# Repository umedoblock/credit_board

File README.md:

# credit_board
This is a credit board. It assure to normal run.

Now credit_board assure you to make some clocks.
Right side can make some clocks that are 10 MHz, 4 MHz, 20 MHz.
Left side can make 32.768 kHz.

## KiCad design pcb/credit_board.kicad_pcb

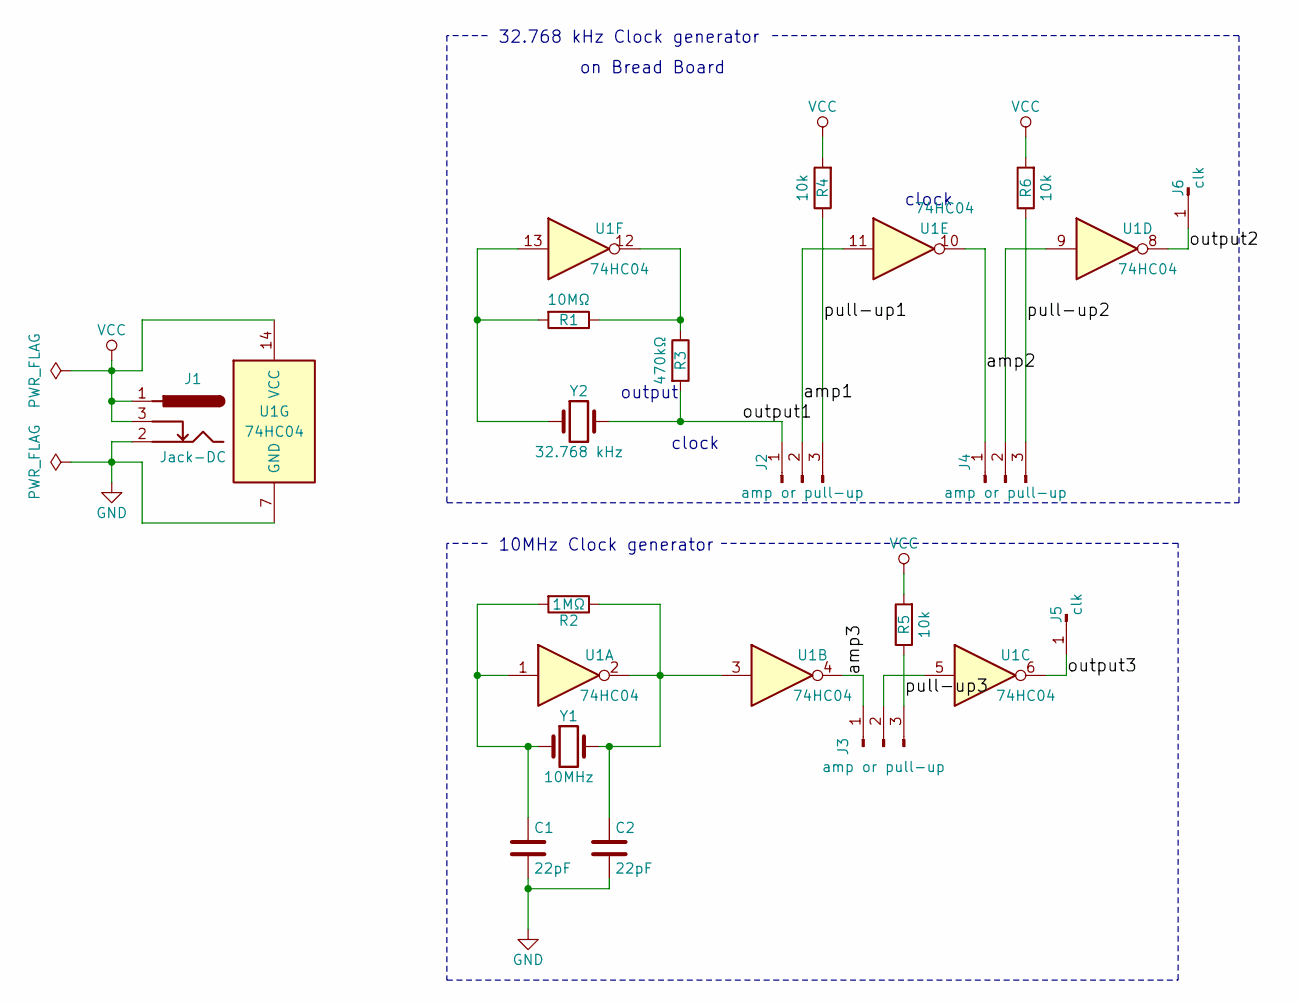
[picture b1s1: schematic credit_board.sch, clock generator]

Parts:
C1, C2: 22pF; C_Disc_D4.7mm_W2.5mm_P5.00mm
J1: Jack-DC; Barrel_Jack_CUI_PJ-102AH
J2, J3, J4: amp or pull-up; Pin_Header_Straight_1x03_Pitch2.54mm
J5, J6: clk; Pin_d1.0mm_L10.0mm
R1: 10MΩ; R_Axial_DIN0207_L6.3mm_D2.5mm_P2.54mm_Vertical
R2: 1MΩ; R_Axial_DIN0207_L6.3mm_D2.5mm_P2.54mm_Vertical
R3: 470kΩ; R_Axial_DIN0207_L6.3mm_D2.5mm_P2.54mm_Vertical
R4, R5, R6: 10k; R_Axial_DIN0207_L6.3mm_D2.5mm_P2.54mm_Vertical
U1: 74HC04; DIP-14_W7.62mm
Y1: 10MHz; Crystal_HC50_Vertical
Y2: 32.768 kHz; Crystal_AT310_d3.0mm_l10.0mm_Vertical

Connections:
/amp1: J2.2, U1.11
/amp2: J4.1, U1.10
/amp3: J3.1, U1.4
/output1: J2.1, R3.2, Y2.2
/output2: J6.1, U1.8
/output3: J5.1, U1.6
/pull-up1: J2.3, R4.1
/pull-up2: J4.3, R6.1
/pull-up3: J3.3, R5.1
GND: C1.2, C2.2, J1.2, U1.7 (GND)
unnamed: C1.1, R2.2, U1.1, Y1.1
unnamed: C2.1, R2.1, U1.2, U1.3, Y1.2
unnamed: J3.2, U1.5
unnamed: J4.2, U1.9
unnamed: R1.1, R3.1, U1.12
unnamed: R1.2, U1.13, Y2.1
VCC: J1.1, J1.3, R4.2, R5.2, R6.2, U1.14 (VCC)

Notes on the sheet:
32.768 kHz Clock generator
10MHz Clock generator
output
on Bread Board
clock

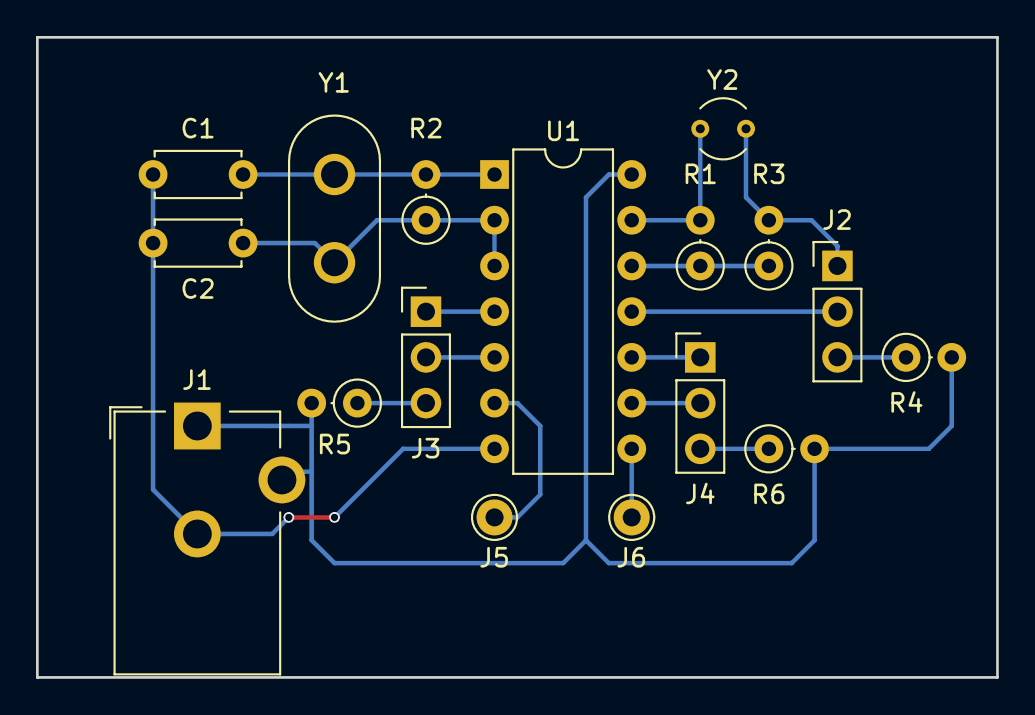
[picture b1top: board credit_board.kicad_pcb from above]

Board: 2 copper layers, 53.3 x 35.6 mm, 17 parts (0 on the bottom side), 17 nets.

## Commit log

2017-09-23 ignore file.
2017-09-23 make clock(10MHz, 32.768kHz) generator board.
    right side can change crystal to 4MHz, 20MHz.
    left size make 32.768kHz clock.
2017-09-23 add ignore file.
2017-09-23 write a description of function about credit_board.
2017-09-23 no connected pins are pull up by 10k resistors.
2017-09-25 74HC04 の input に未接続の端子は，pull up するようにした。
2017-09-25 completed to make a initial credit board.
2017-09-25 細かな修正。これで本当に完成。
2017-09-25 本当の，本当に完成したよぉぉぉぉ。
    神経質には完成させられないんじゃないだろうか？と完成を危ぶんだこともありました。
    しかし，なんとか完成しました。
    めでたし。めでたし。
2017-10-06 beta ground にした。
2017-10-07 board の clock 部は完成。
2017-10-07 U1 GND, J1 GND の接続にViaを使用した。
2017-10-07 自作のuni板と，kicadの設計board。
2018-02-14 Jack-DCの3PINを未接続にした。
